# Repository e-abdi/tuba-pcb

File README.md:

# Tuba Electronics PCB

## Photos

### Front

### Back

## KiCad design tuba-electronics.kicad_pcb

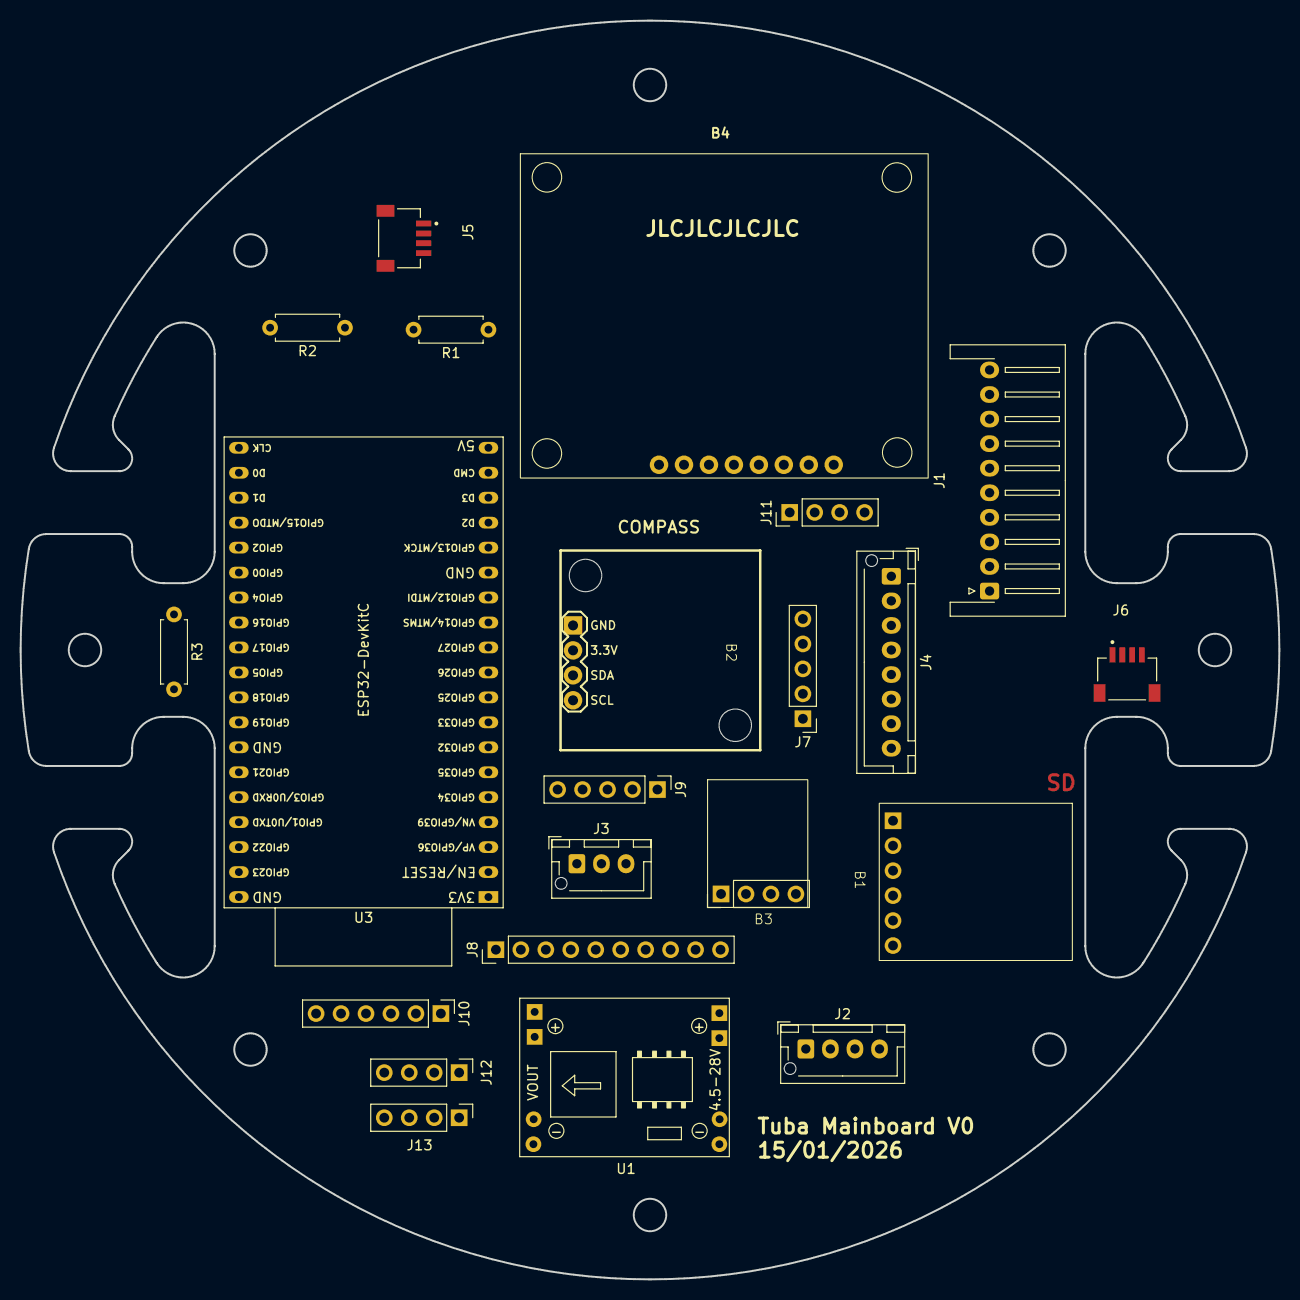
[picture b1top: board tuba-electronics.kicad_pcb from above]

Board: 2 copper layers, 128.1 x 128.1 mm, 22 parts (0 on the bottom side), 47 nets, no tracks yet.

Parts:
B1: OpenLog
B2: HMC6343
B3: BMP180; bmp180
B4: neo-m8u
J1: Conn_01x10; JST_XH_S10B-XH-A-1_1x10_P2.50mm_Horizontal
J2: Conn_01x04; JST_XH_B4B-XH-AM_1x04_P2.50mm_Vertical
J3: Conn_01x03; JST_XH_B3B-XH-AM_1x03_P2.50mm_Vertical
J4: Conn_01x08; JST_XH_B8B-XH-AM_1x08_P2.50mm_Vertical
J5, J6: Qwiic_Connector; Qwiic
J7, J9: Conn_01x05; PinHeader_1x05_P2.54mm_Vertical
J8: Conn_01x10; PinHeader_1x10_P2.54mm_Vertical
J10: Conn_01x06; PinHeader_1x06_P2.54mm_Vertical
J11, J12, J13: Conn_01x04; PinHeader_1x04_P2.54mm_Vertical
R1, R2, R3: R; R_Axial_DIN0207_L6.3mm_D2.5mm_P7.62mm_Horizontal
U1: MP1584; SRT_MPT1584EN_Module
U3: ESP32-DevKitC

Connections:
+3V3: B1.4 (VCC), B2.2 (3V3), B3.1 (Vin), B4.3 (3V3), J2.1, J5.2, J6.2, J12.3, J12.4, R2.2, R3.2, U3.1 (3V3)
+5V: J12.2, U1.5 (OUT+), U1.6 (OUT+), U3.19 (5V)
/ENDSTOP_AFT: J1.9, R3.1, U3.21 (SD_DATA0/GPIO7)
/ENDSTOP_FOR: J3.1, R2.1, U3.20 (SD_CLK/GPIO6)
/I2C_SCL: B2.4 (SCL), B3.3 (SCL), B4.1 (SCL), J2.2, J5.4, J6.4, U3.36 (GPIO22)
/I2C_SDA: B2.3 (SDA), B3.4 (SDA), B4.2 (SDA), J2.3, J5.3, J6.3, U3.33 (GPIO21)
/IN1_P: J1.2, U3.30 (GPIO18)
/IN1_RP: J1.4, U3.9 (DAC_1/ADC2_CH8/GPIO25)
/IN2_P: J1.3, U3.31 (GPIO19)
/IN2_RP: J1.5, U3.10 (DAC_2/ADC2_CH9/GPIO26)
/IN3_RP: J1.6, U3.11 (ADC2_CH7/GPIO27)
/IN4_RP: J1.7, U3.12 (MTMS/GPIO14/ADC2_CH6)
/RX0: B1.2 (RX), U3.34 (U0RXD/GPIO3)
/SWITCH_1: J4.2, R1.2
/SWITCH_2: J1.8, J4.3, J7.5
/TX0: B1.3 (TX), U3.35 (U0TXD/GPIO1)
GND: B1.5 (GND), B2.1 (GND), B3.2 (GND), B4.4 (GND), J1.10, J2.4, J3.3, J4.8, J5.1, J6.1, J13.1, J13.2, J13.3, J13.4, U1.3 (IN-), U1.4 (IN-), U1.7 (OUT-), U1.8 (OUT-), U3.14 (GND), U3.32 (GND), U3.38 (GND)
unnamed: B4.5 (INT), J11.4
unnamed: B4.8 (PPS), J11.1
unnamed: B4.7 (RST), J11.2
unnamed: B4.6 (SAFE), J11.3
unnamed: J4.4, J7.4
unnamed: J4.5, J7.3
unnamed: J4.6, J7.2
unnamed: J4.7, J7.1
unnamed: J8.1, U3.4 (SENSOR_VN/GPIO39/ADC1_CH3)
unnamed: J8.2, U3.3 (SENSOR_VP/GPIO36/ADC1_CH0)
unnamed: J8.3, U3.6 (VDET_2/GPIO35/ADC1_CH7)
unnamed: J8.4, U3.5 (VDET_1/GPIO34/ADC1_CH6)
unnamed: J8.5, U3.23 (MTDO/GPIO15/ADC2_CH3)
unnamed: J8.6, U3.15 (MTCK/GPIO13/ADC2_CH4)
unnamed: J8.7, U3.13 (MTDI/GPIO12/ADC2_CH5)
unnamed: J8.8, U3.8 (32K_XN/GPIO33/ADC1_CH5)
unnamed: J8.9, U3.7 (32K_XP/GPIO32/ADC1_CH4)
unnamed: J8.10, U3.2 (CHIP_PU)
unnamed: J9.1, U3.25 (GPIO0/BOOT/ADC2_CH1)
unnamed: J9.2, U3.24 (ADC2_CH2/GPIO2)
unnamed: J9.3, U3.26 (ADC2_CH0/GPIO4)
unnamed: J9.4, U3.29 (GPIO5)
unnamed: J9.5, U3.37 (GPIO23)
unnamed: J10.1, U3.22 (SD_DATA1/GPIO8)
unnamed: J10.2, U3.16 (SD_DATA2/GPIO9)
unnamed: J10.3, U3.17 (SD_DATA3/GPIO10)
unnamed: J10.4, U3.18 (CMD)
unnamed: J10.5, U3.27 (GPIO16)
unnamed: J10.6, U3.28 (GPIO17)
VCC: J1.1, J4.1, J12.1, R1.1, U1.1 (IN+), U1.2 (IN+)

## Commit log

2026-01-15 tuba pcb v0
2026-01-29 changed limit switches GPIOs, added pics
2026-01-29 pics
2026-02-05 adding BOM
